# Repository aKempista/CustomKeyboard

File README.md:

# CustomKeyboard
 A repository of custom keyboard kicad projects.

## Key Components
- ATMEGA32U4-AU
- QMK Firmware
- JLCPCB for Manufacturing
- 1/16" Aluminum Plate
- 1/16" Wood Veneer

## Notes
- Focus on Plate Mount Hotswap switches, but support PCB mount as well for better design flexibility.
- Exploded 75% layout is ideal.

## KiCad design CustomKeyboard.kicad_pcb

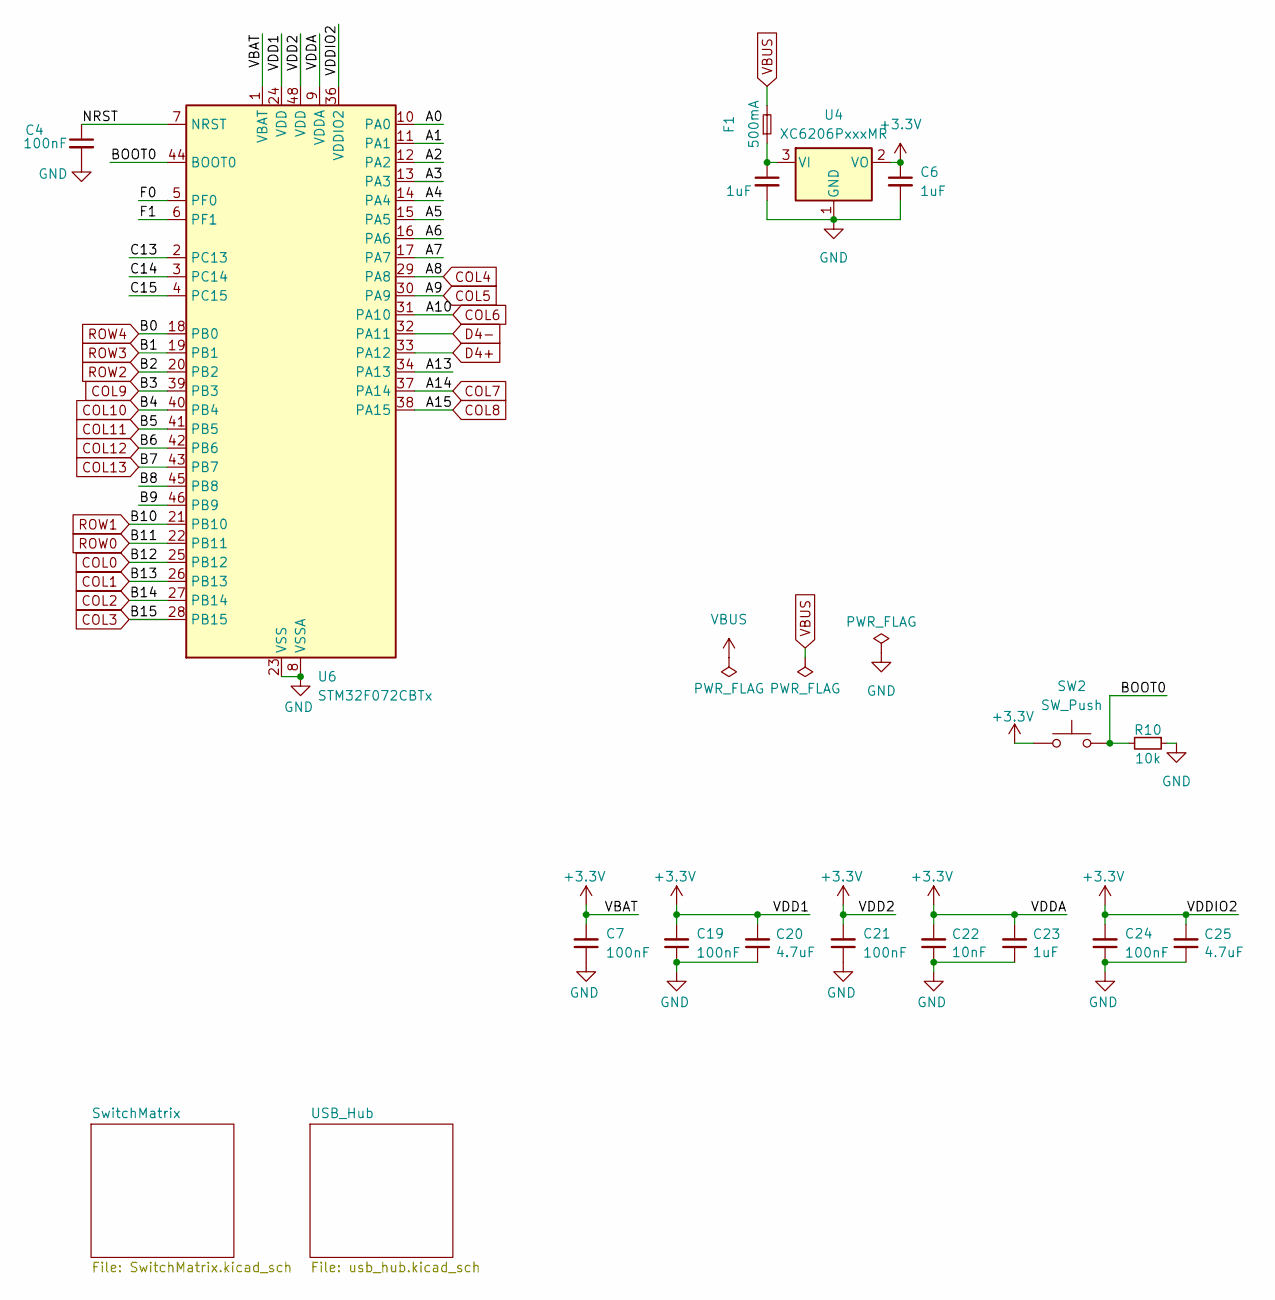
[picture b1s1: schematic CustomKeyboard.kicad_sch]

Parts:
C4: 100nF; C_0402_1005Metric; LCSC C307331
C5, C6: 1uF; C_0402_1005Metric; LCSC C52923
C7, C19, C21, C24: 100nF; C_0402_1005Metric; MPN CL05B104KB54PNC; LCSC C307331
C20, C25: 4.7uF; C_0402_1005Metric; MPN CL05A475MP5NRNC; LCSC C23733
C22: 10nF; C_0402_1005Metric; MPN CL05B103KB5NNNC; LCSC C15195
C23: 1uF; C_0402_1005Metric; MPN CL05A105KA5NQNC; LCSC C52923
F1: 500mA; Fuse_0603_1608Metric; LCSC C210357
R10: 10k; R_0402_1005Metric; LCSC C25744
SW2: SW_Push; SKQG-1155865
U4: XC6206PxxxMR; SOT-23-3
U6: STM32F072CBTx; LQFP-48_7x7mm_P0.5mm

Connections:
+3.3V: C6.1, C7.2, C19.2, C20.2, C21.2, C22.2, C23.2, C24.2, C25.2, SW2.1, U4.2 (VO), U6.1 (VBAT), U6.9 (VDDA), U6.24 (VDD), U6.36 (VDDIO2), U6.48 (VDD)
/A0: U6.10 (PA0)
/A1: U6.11 (PA1)
/A2: U6.12 (PA2)
/A3: U6.13 (PA3)
/A4: U6.14 (PA4)
/A5: U6.15 (PA5)
/A6: U6.16 (PA6)
/A7: U6.17 (PA7)
/A13: U6.34 (PA13)
/B8: U6.45 (PB8)
/B9: U6.46 (PB9)
/BOOT0: R10.2, SW2.2, U6.44 (BOOT0)
/C13: U6.2 (PC13)
/C14: U6.3 (PC14)
/C15: U6.4 (PC15)
/F0: U6.5 (PF0)
/F1: U6.6 (PF1)
/NRST: C4.1, U6.7 (NRST)
COL0: U6.25 (PB12); also elsewhere on the board
COL1: U6.26 (PB13); also elsewhere on the board
COL2: U6.27 (PB14); also elsewhere on the board
COL3: U6.28 (PB15); also elsewhere on the board
COL4: U6.29 (PA8); also elsewhere on the board
COL5: U6.30 (PA9); also elsewhere on the board
COL6: U6.31 (PA10); also elsewhere on the board
COL7: U6.37 (PA14); also elsewhere on the board
COL8: U6.38 (PA15); also elsewhere on the board
COL9: U6.39 (PB3); also elsewhere on the board
COL10: U6.40 (PB4); also elsewhere on the board
COL11: U6.41 (PB5); also elsewhere on the board
COL12: U6.42 (PB6); also elsewhere on the board
COL13: U6.43 (PB7); also elsewhere on the board
D4+: U6.33 (PA12); also elsewhere on the board
D4-: U6.32 (PA11); also elsewhere on the board
GND: C4.2, C5.2, C6.2, C7.1, C19.1, C20.1, C21.1, C22.1, C23.1, C24.1, C25.1, R10.1, U4.1 (GND), U6.8 (VSSA), U6.23 (VSS), U6.35 (VSS), U6.47 (VSS); also elsewhere on the board
unnamed: C5.1, F1.1, U4.3 (VI)
ROW0: U6.22 (PB11); also elsewhere on the board
ROW1: U6.21 (PB10); also elsewhere on the board
ROW2: U6.20 (PB2); also elsewhere on the board
ROW3: U6.19 (PB1); also elsewhere on the board
ROW4: U6.18 (PB0); also elsewhere on the board
VBUS: F1.2; also elsewhere on the board

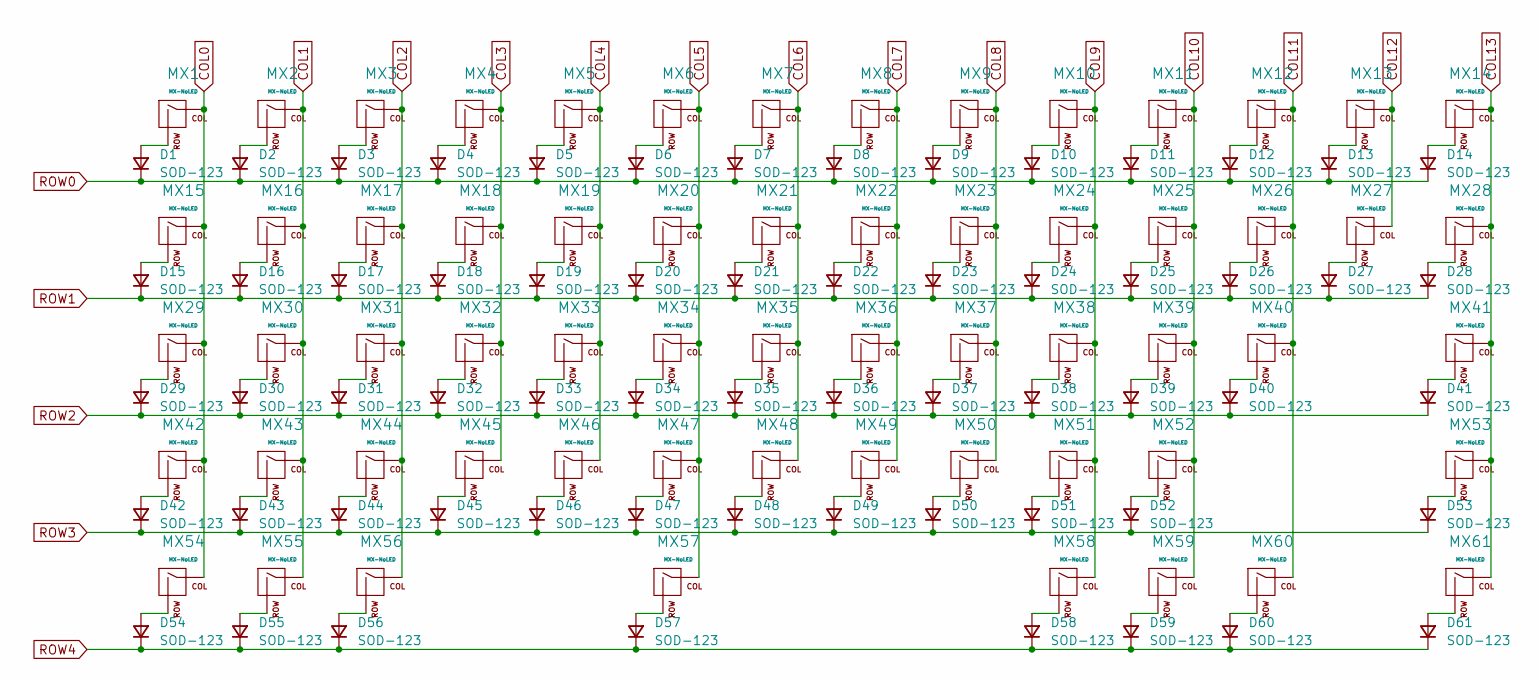
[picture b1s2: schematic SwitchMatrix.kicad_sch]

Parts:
D1, D2, D3, D4, D5, D6, D7, D8, D9, D10, D11, D12, D13, D14, D15, D16, D17, D18, D19, D20, D21, D22, D23, D24, D25, D26, D27, D28, D29, D30, D31, D32, D33, D34, D35, D36, D37, D38, D39, D40, D41, D42, D43, D44, D45, D46, D47, D48, D49, D50, D51, D52, D53, D54, D55, D56, D57, D58, D59, D60, D61: SOD-123; D_SOD-123
MX1, MX2, MX3, MX4, MX5, MX6, MX7, MX8, MX9, MX10, MX11, MX12, MX13, MX14, MX15, MX16, MX17, MX18, MX19, MX20, MX21, MX22, MX23, MX24, MX25, MX26, MX27, MX28, MX29, MX30, MX31, MX32, MX33, MX34, MX35, MX36, MX37, MX38, MX39, MX40, MX41, MX42, MX43, MX44, MX45, MX46, MX47, MX48, MX49, MX50, MX51, MX52, MX53, MX54, MX55, MX56, MX57, MX58, MX59, MX60, MX61: MX-NoLED; SW_MX_HS_CPG151101S11_1u

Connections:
COL0: MX1.1 (COL), MX15.1 (COL), MX29.1 (COL), MX42.1 (COL), MX54.1 (COL); also elsewhere on the board
COL1: MX2.1 (COL), MX16.1 (COL), MX30.1 (COL), MX43.1 (COL), MX55.1 (COL); also elsewhere on the board
COL2: MX3.1 (COL), MX17.1 (COL), MX31.1 (COL), MX44.1 (COL), MX56.1 (COL); also elsewhere on the board
COL3: MX4.1 (COL), MX18.1 (COL), MX32.1 (COL), MX45.1 (COL); also elsewhere on the board
COL4: MX5.1 (COL), MX19.1 (COL), MX33.1 (COL), MX46.1 (COL); also elsewhere on the board
COL5: MX6.1 (COL), MX20.1 (COL), MX34.1 (COL), MX47.1 (COL), MX57.1 (COL); also elsewhere on the board
COL6: MX7.1 (COL), MX21.1 (COL), MX35.1 (COL), MX48.1 (COL); also elsewhere on the board
COL7: MX8.1 (COL), MX22.1 (COL), MX36.1 (COL), MX49.1 (COL); also elsewhere on the board
COL8: MX9.1 (COL), MX23.1 (COL), MX37.1 (COL), MX50.1 (COL); also elsewhere on the board
COL9: MX10.1 (COL), MX24.1 (COL), MX38.1 (COL), MX51.1 (COL), MX58.1 (COL); also elsewhere on the board
COL10: MX11.1 (COL), MX25.1 (COL), MX39.1 (COL), MX52.1 (COL), MX59.1 (COL); also elsewhere on the board
COL11: MX12.1 (COL), MX26.1 (COL), MX40.1 (COL), MX60.1 (COL); also elsewhere on the board
COL12: MX13.1 (COL), MX27.1 (COL); also elsewhere on the board
COL13: MX14.1 (COL), MX28.1 (COL), MX41.1 (COL), MX53.1 (COL), MX61.1 (COL); also elsewhere on the board
unnamed: D1.2 (A), MX1.2 (ROW)
unnamed: D2.2 (A), MX2.2 (ROW)
unnamed: D3.2 (A), MX3.2 (ROW)
unnamed: D4.2 (A), MX4.2 (ROW)
unnamed: D5.2 (A), MX5.2 (ROW)
unnamed: D6.2 (A), MX6.2 (ROW)
unnamed: D7.2 (A), MX7.2 (ROW)
unnamed: D8.2 (A), MX8.2 (ROW)
unnamed: D9.2 (A), MX9.2 (ROW)
unnamed: D10.2 (A), MX10.2 (ROW)
unnamed: D11.2 (A), MX11.2 (ROW)
unnamed: D12.2 (A), MX12.2 (ROW)
unnamed: D13.2 (A), MX13.2 (ROW)
unnamed: D14.2 (A), MX14.2 (ROW)
unnamed: D15.2 (A), MX15.2 (ROW)
unnamed: D16.2 (A), MX16.2 (ROW)
unnamed: D17.2 (A), MX17.2 (ROW)
unnamed: D18.2 (A), MX18.2 (ROW)
unnamed: D19.2 (A), MX19.2 (ROW)
unnamed: D20.2 (A), MX20.2 (ROW)
unnamed: D21.2 (A), MX21.2 (ROW)
unnamed: D22.2 (A), MX22.2 (ROW)
unnamed: D23.2 (A), MX23.2 (ROW)
unnamed: D24.2 (A), MX24.2 (ROW)
unnamed: D25.2 (A), MX25.2 (ROW)
unnamed: D26.2 (A), MX26.2 (ROW)
unnamed: D27.2 (A), MX27.2 (ROW)
unnamed: D28.2 (A), MX28.2 (ROW)
unnamed: D29.2 (A), MX29.2 (ROW)
unnamed: D30.2 (A), MX30.2 (ROW)
unnamed: D31.2 (A), MX31.2 (ROW)
unnamed: D32.2 (A), MX32.2 (ROW)
unnamed: D33.2 (A), MX33.2 (ROW)
unnamed: D34.2 (A), MX34.2 (ROW)
unnamed: D35.2 (A), MX35.2 (ROW)
unnamed: D36.2 (A), MX36.2 (ROW)
unnamed: D37.2 (A), MX37.2 (ROW)
unnamed: D38.2 (A), MX38.2 (ROW)
unnamed: D39.2 (A), MX39.2 (ROW)
unnamed: D40.2 (A), MX40.2 (ROW)
unnamed: D41.2 (A), MX41.2 (ROW)
unnamed: D42.2 (A), MX42.2 (ROW)
unnamed: D43.2 (A), MX43.2 (ROW)
unnamed: D44.2 (A), MX44.2 (ROW)
unnamed: D45.2 (A), MX45.2 (ROW)
unnamed: D46.2 (A), MX46.2 (ROW)
unnamed: D47.2 (A), MX47.2 (ROW)
unnamed: D48.2 (A), MX48.2 (ROW)
unnamed: D49.2 (A), MX49.2 (ROW)
unnamed: D50.2 (A), MX50.2 (ROW)
unnamed: D51.2 (A), MX51.2 (ROW)
unnamed: D52.2 (A), MX52.2 (ROW)
unnamed: D53.2 (A), MX53.2 (ROW)
unnamed: D54.2 (A), MX54.2 (ROW)
unnamed: D55.2 (A), MX55.2 (ROW)
unnamed: D56.2 (A), MX56.2 (ROW)
unnamed: D57.2 (A), MX57.2 (ROW)
unnamed: D58.2 (A), MX58.2 (ROW)
unnamed: D59.2 (A), MX59.2 (ROW)
unnamed: D60.2 (A), MX60.2 (ROW)
unnamed: D61.2 (A), MX61.2 (ROW)
ROW0: D1.1 (K), D2.1 (K), D3.1 (K), D4.1 (K), D5.1 (K), D6.1 (K), D7.1 (K), D8.1 (K), D9.1 (K), D10.1 (K), D11.1 (K), D12.1 (K), D13.1 (K), D14.1 (K); also elsewhere on the board
ROW1: D15.1 (K), D16.1 (K), D17.1 (K), D18.1 (K), D19.1 (K), D20.1 (K), D21.1 (K), D22.1 (K), D23.1 (K), D24.1 (K), D25.1 (K), D26.1 (K), D27.1 (K), D28.1 (K); also elsewhere on the board
ROW2: D29.1 (K), D30.1 (K), D31.1 (K), D32.1 (K), D33.1 (K), D34.1 (K), D35.1 (K), D36.1 (K), D37.1 (K), D38.1 (K), D39.1 (K), D40.1 (K), D41.1 (K); also elsewhere on the board
ROW3: D42.1 (K), D43.1 (K), D44.1 (K), D45.1 (K), D46.1 (K), D47.1 (K), D48.1 (K), D49.1 (K), D50.1 (K), D51.1 (K), D52.1 (K), D53.1 (K); also elsewhere on the board
ROW4: D54.1 (K), D55.1 (K), D56.1 (K), D57.1 (K), D58.1 (K), D59.1 (K), D60.1 (K), D61.1 (K); also elsewhere on the board

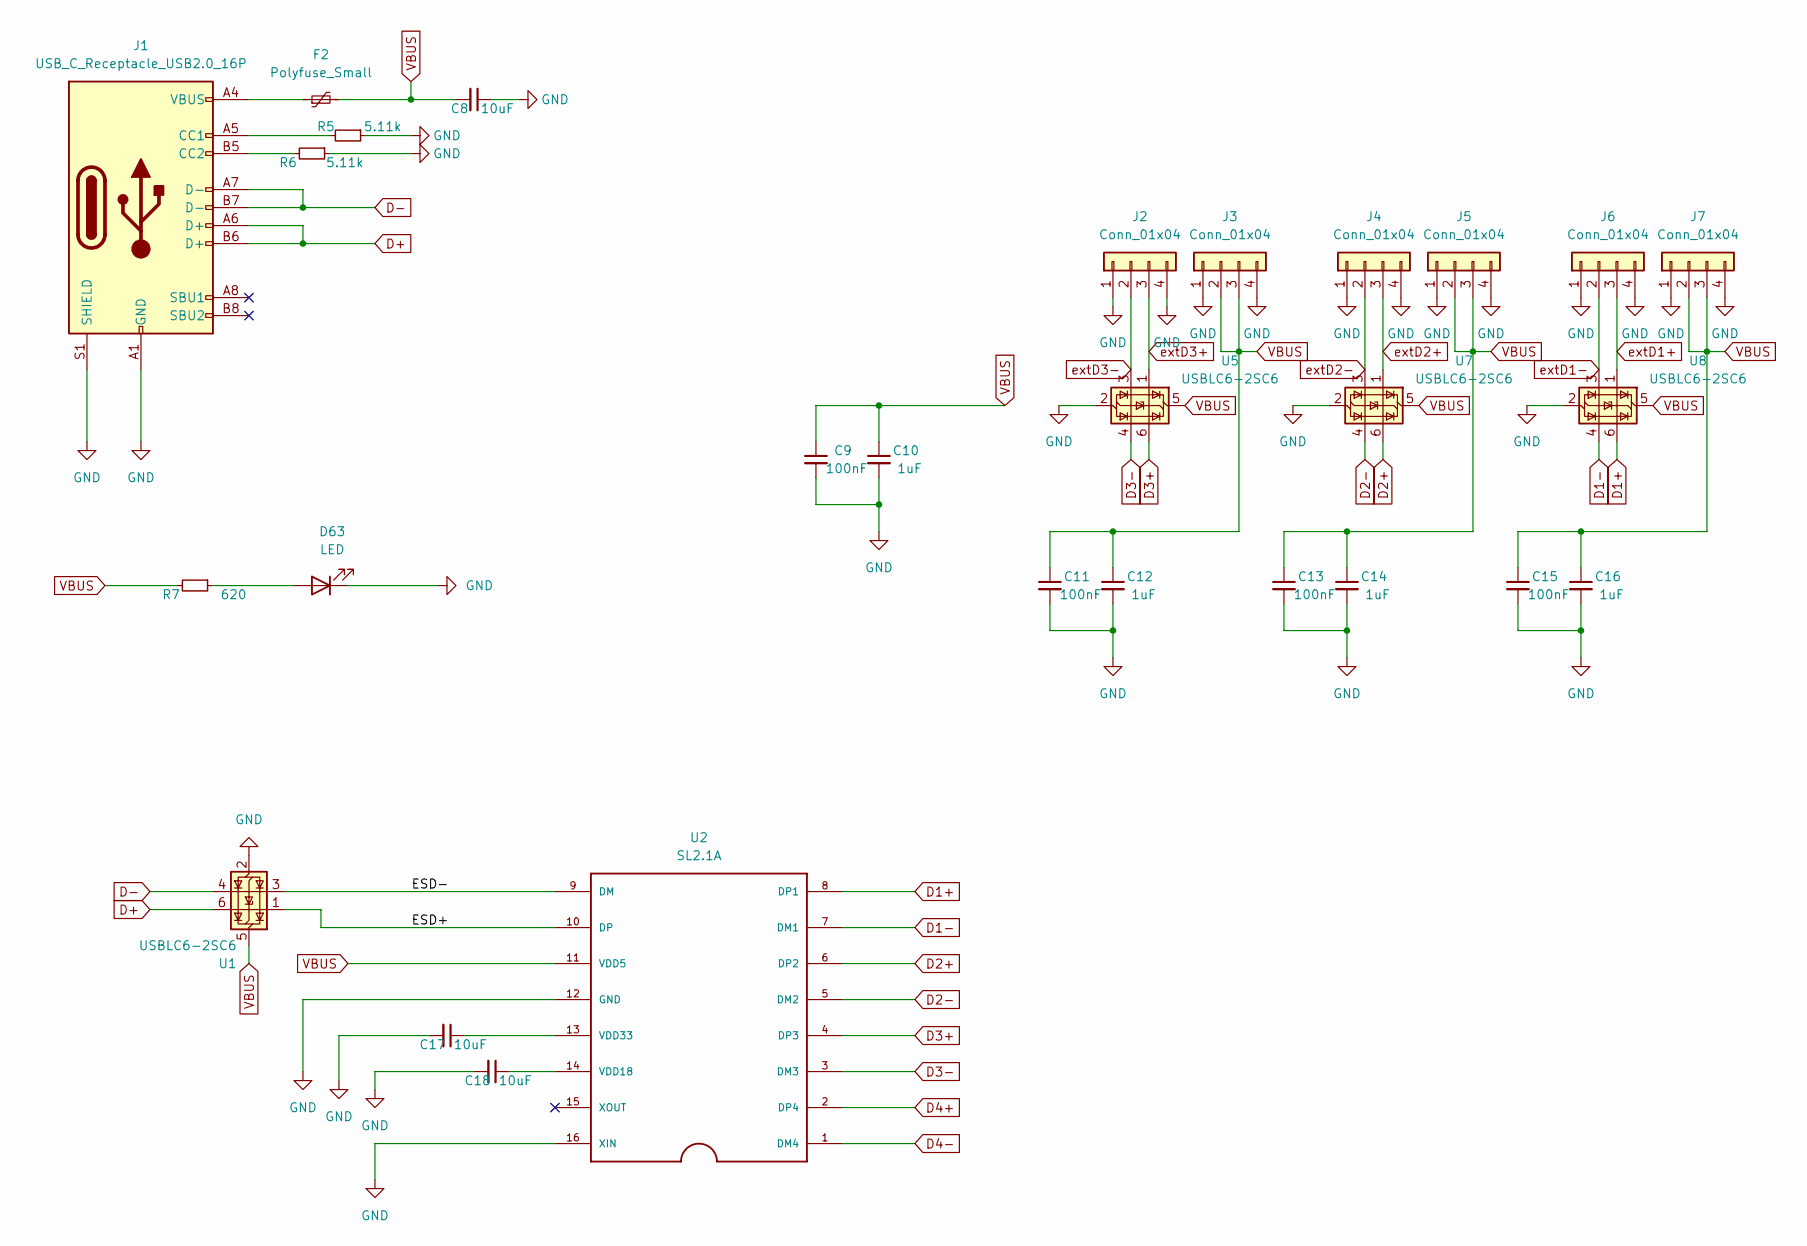
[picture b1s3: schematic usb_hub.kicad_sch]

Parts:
C8, C17, C18: 10uF; C_0603_1608Metric
C9, C11, C13, C15: 100nF; C_0603_1608Metric
C10, C12, C14, C16: 1uF; C_0603_1608Metric
D63: LED; LED_0805_2012Metric; MPN C98224
F2: Polyfuse_Small; Fuse_1206_3216Metric
J1: USB_C_Receptacle_USB2.0_16P; USB_C_Receptacle_GCT_USB4105-xx-A_16P_TopMnt_Horizontal
J2, J3, J4, J5, J6, J7: Conn_01x04; 4_Pad_2.54_Exposed
R5, R6: 5.11k; R_0805_2012Metric
R7: 620; R_0603_1608Metric
U1, U5, U7, U8: USBLC6-2SC6; SOT-23-6
U2: SL2.1A; SO16; MPN C6798314

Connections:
/USB_Hub/ESD+: U1.1 (I/O1), U2.10 (DP)
/USB_Hub/ESD-: U1.3 (I/O2), U2.9 (DM)
D1+: U2.8 (DP1), U8.6 (I/O1)
D1-: U2.7 (DM1), U8.4 (I/O2)
D2+: U2.6 (DP2), U7.6 (I/O1)
D2-: U2.5 (DM2), U7.4 (I/O2)
D3+: U2.4 (DP3), U5.6 (I/O1)
D3-: U2.3 (DM3), U5.4 (I/O2)
D4+: U2.2 (DP4); also elsewhere on the board
D4-: U2.1 (DM4); also elsewhere on the board
D+: J1.A6 (D+), J1.B6 (D+), U1.6 (I/O1)
D-: J1.A7 (D-), J1.B7 (D-), U1.4 (I/O2)
GND: C8.1, C9.2, C10.2, C11.2, C12.2, C13.2, C14.2, C15.2, C16.2, C17.2, C18.2, D63.1 (K), J1.A1 (GND), J1.A12 (GND), J1.B1 (GND), J1.B12 (GND), J1.S1 (SHIELD), J2.1, J2.4, J3.1, J3.4, J4.1, J4.4, J5.1, J5.4, J6.1, J6.4, J7.1, J7.4, R5.1, R6.1, U1.2 (GND), U2.12 (GND), U2.16 (XIN), U5.2 (GND), U7.2 (GND), U8.2 (GND); also elsewhere on the board
unnamed: D63.2 (A), R7.1
unnamed: F2.1, J1.A4 (VBUS), J1.A9 (VBUS), J1.B4 (VBUS), J1.B9 (VBUS)
unnamed: J1.A5 (CC1), R5.2
unnamed: J1.B5 (CC2), R6.2
unnamed: C18.1, U2.14 (VDD18)
unnamed: C17.1, U2.13 (VDD33)
VBUS: C8.2, C9.1, C10.1, C11.1, C12.1, C13.1, C14.1, C15.1, C16.1, F2.2, J3.2, J3.3, J5.2, J5.3, J7.2, J7.3, R7.2, U1.5 (VBUS), U2.11 (VDD5), U5.5 (VBUS), U7.5 (VBUS), U8.5 (VBUS); also elsewhere on the board
extD1+: J6.3, U8.1 (I/O1)
extD1-: J6.2, U8.3 (I/O2)
extD2+: J4.3, U7.1 (I/O1)
extD2-: J4.2, U7.3 (I/O2)
extD3+: J2.3, U5.1 (I/O1)
extD3-: J2.2, U5.3 (I/O2)

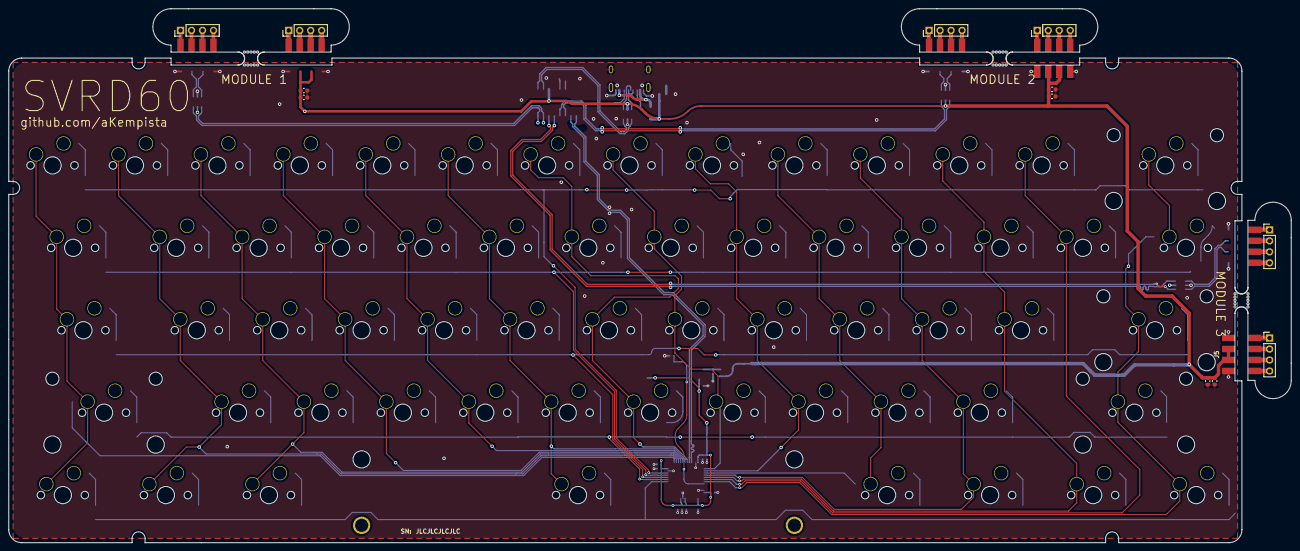
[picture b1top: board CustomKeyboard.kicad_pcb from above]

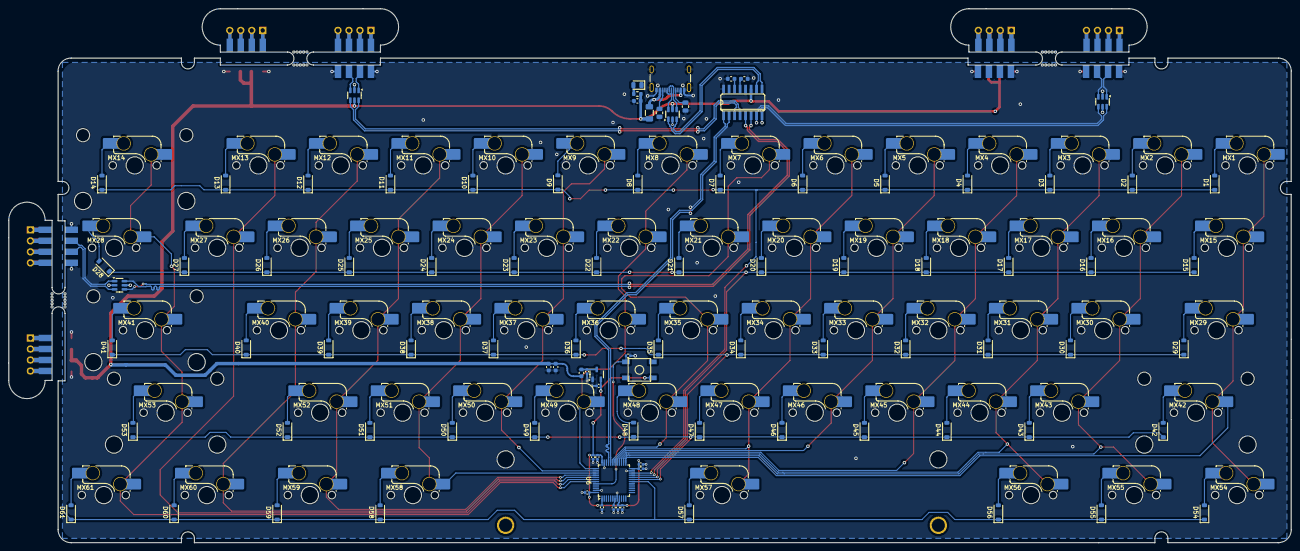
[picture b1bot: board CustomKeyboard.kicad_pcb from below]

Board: 2 copper layers, 296.4 x 123.4 mm, 169 parts (158 on the bottom side), 110 nets.

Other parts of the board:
mouse-bite-3mm-slot, mouse-bite-3mm-slot#2, mouse-bite-3mm-slot#3: VAL**; mouse-bite-3mm-slot

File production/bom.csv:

Designator,Footprint,Quantity,Value,LCSC Part #
"C1, C2",0805,2,22pF,
"C10, C12, C14, C16, C3",0805,5,1uF,
"C11, C13, C15, C9",0805,4,100nF,
"C17, C18, C8",0805,3,10uF,
"D1, D10, D11, D12, D13, D14, D15, D16, D17, D18, D19, D2, D20, D21, D22, D23, D24, D25, D26, D27, D28, D29, D3, D30, D31, D32, D33, D34, D35, D36, D37, D38, D39, D4, D40, D41, D42, D43, D44, D45, D46, D47, D48, D49, D5, D50, D51, D52, D53, D54, D55, D56, D57, D58, D59, D6, D60, D61, D7, D8, D9",D_SOD-123,61,SOD-123,
D62,D_SMA,1,SS14,C3015375
D63,0805,1,LED,C98224
J1,USB_C_Receptacle_GCT_USB4105-xx-A_16P_TopMnt_Horizontal,1,USB_C_Receptacle_USB2.0_16P,
"J2, J3, J4, J5, J6, J7",PinHeader_1x04_P2.54mm_Vertical,6,Conn_01x04,
"MX1, MX10, MX11, MX12, MX13, MX14, MX15, MX16, MX17, MX18, MX19, MX2, MX20, MX21, MX22, MX23, MX24, MX25, MX26, MX27, MX28, MX29, MX3, MX30, MX31, MX32, MX33, MX34, MX35, MX36, MX37, MX38, MX39, MX4, MX40, MX41, MX42, MX43, MX44, MX45, MX46, MX47, MX48, MX49, MX5, MX50, MX51, MX52, MX53, MX54, MX55, MX56, MX57, MX58, MX59, MX6, MX60, MX61, MX7, MX8, MX9",Kailh_socket_MX,61,MX-NoLED,
"R1, R4",0805,2,10k,
"R2, R3",0805,2,22,
"R5, R6",0805,2,5.11k,
R7,0603,1,620,
SW1,SKQG-1155865,1,SW_Push,
U1,TQFP-44_10x10mm_P0.8mm,1,ATmega32U4-A,
U2,SO16,1,SL2.1A,C6798314
Y1,Crystal_SMD_3225-4Pin_3.2x2.5mm,1,16MHz,

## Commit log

2025-02-04 recorrected file organization
2025-02-09 started pcb
2025-02-28 many things changed
